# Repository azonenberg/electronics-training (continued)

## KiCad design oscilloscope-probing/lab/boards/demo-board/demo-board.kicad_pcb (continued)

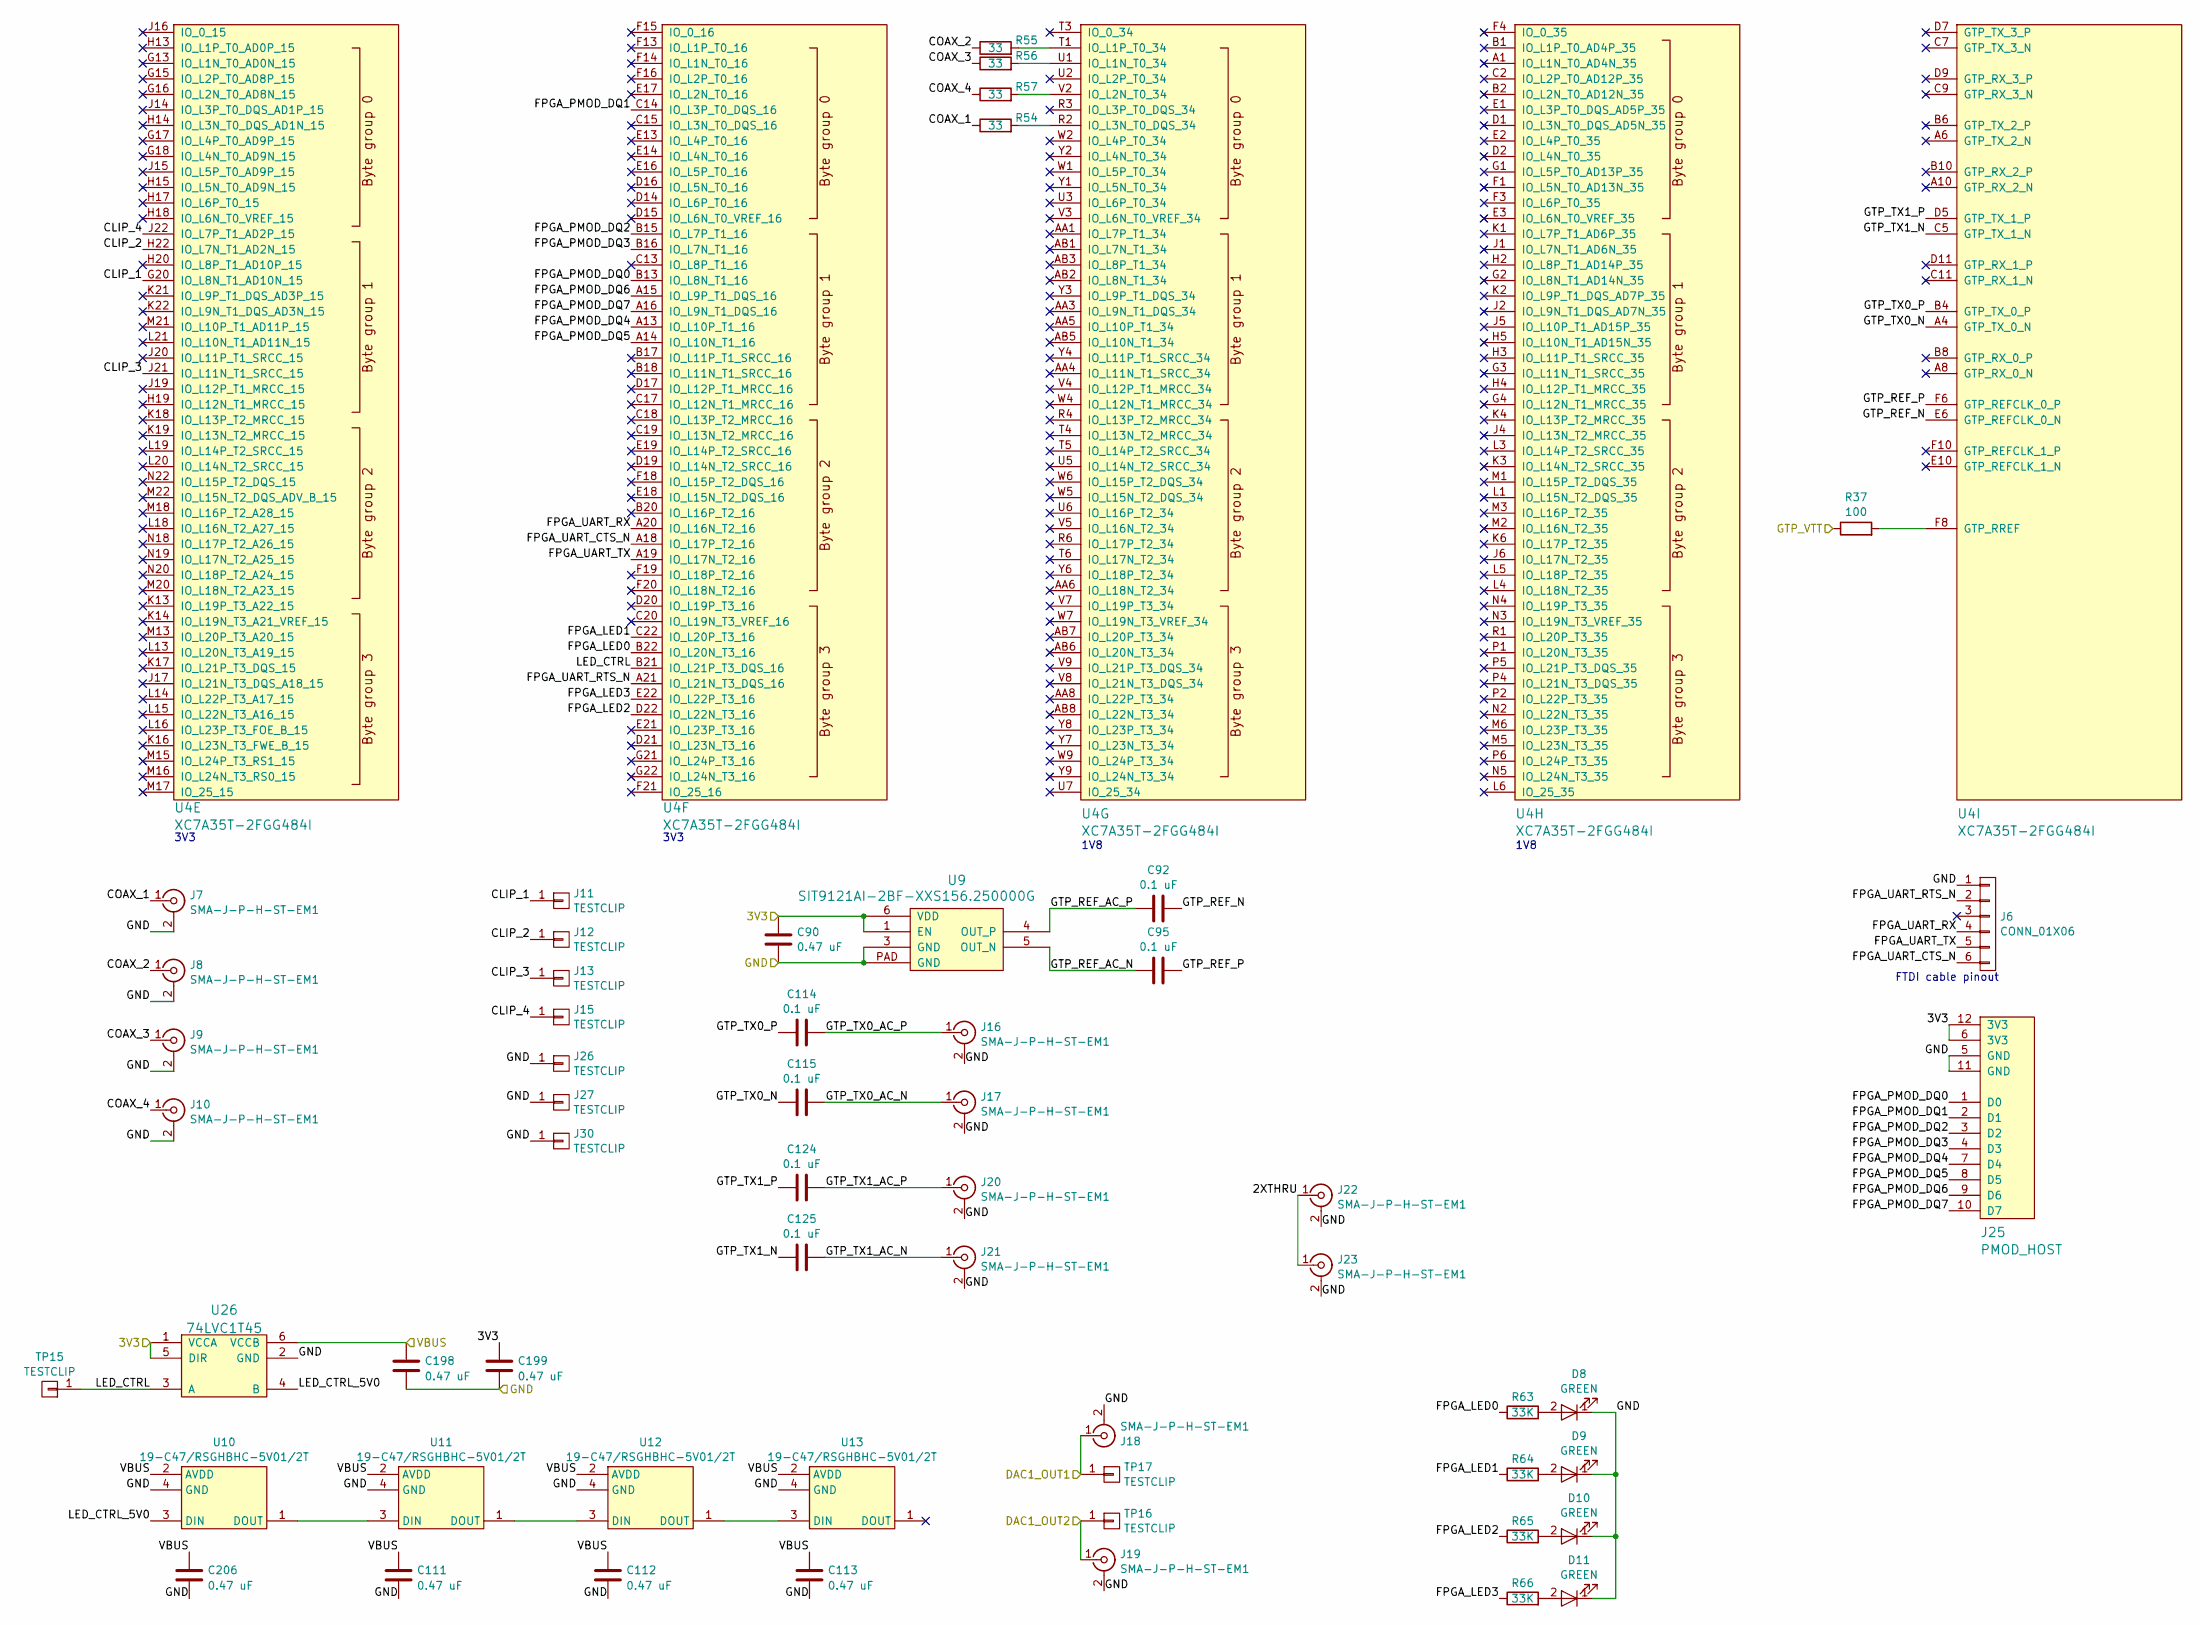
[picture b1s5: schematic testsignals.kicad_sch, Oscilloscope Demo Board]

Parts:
C90, C111, C112, C113, C198, C199, C206: 0.47 uF; EIA_0402_CAP_NOSILK
C92, C95, C114, C115, C124, C125: 0.1 uF; EIA_0402_CAP_NOSILK
D8, D9, D10, D11: GREEN; EIA_0402_LED
J6: CONN_01X06; CONN_HEADER_2.54MM_1x6_REFLOW
J7, J8, J9, J10, J16, J17, J20, J21: SMA-J-P-H-ST-EM1; CONN_SMA_EDGE_SAMTEC_SMA_J_P_H_ST_EM1
J11, J12, J13, J15, J26, J27, J30: TESTCLIP; TESTPOINT_SMT_KEYSTONE_5016
J18, J19, J22, J23: SMA-J-P-H-ST-EM1; CONN_SMA_EDGE_SAMTEC_SMA_J_P_H_ST_EM1_NOPASTE
J25: PMOD_HOST; CONN_HEADER_2.54MM_2x6_RA_PMOD_HOST
R37: 100; EIA_0402_RES_NOSILK
R54, R55, R56, R57: 33; EIA_0402_RES_NOSILK
R63, R64, R65, R66: 33K; EIA_0402_RES_NOSILK
TP15, TP16, TP17: TESTCLIP; TESTPOINT_SMT_KEYSTONE_5016
U4: XC7A35T-2FGG484I; BGA_484_22x22_FULLARRAY_1MM
U9: SIT9121AI-2BF-XXS156.250000G; OSCILLATOR_LVDS_3.2x2.5
U10, U11, U12, U13: 19-C47/RSGHBHC-5V01/2T; LED_EVERLIGHT_19-C47_RSGHBHC-5V01_2T
U26: 74LVC1T45; DFN_6_0.5MM_1.6x1.6MM_TI_DPK

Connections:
/1V2: R37.1; also elsewhere on the board
/3V3: C90.1, C199.1, J25.6 (3V3), J25.12 (3V3), U9.1 (EN), U9.6 (VDD), U26.1 (VCCA), U26.5 (DIR); also elsewhere on the board
/GND: C90.2, C111.2, C112.2, C113.2, C198.2, C199.2, C206.2, D8.1 (K), D9.1 (K), D10.1 (K), D11.1 (K), J6.1, J7.2 (Ext), J8.2 (Ext), J9.2 (Ext), J10.2 (Ext), J16.2 (Ext), J17.2 (Ext), J18.2 (Ext), J19.2 (Ext), J20.2 (Ext), J21.2 (Ext), J22.2 (Ext), J23.2 (Ext), J25.5 (GND), J25.11 (GND), J26.1, J27.1, J30.1, U9.3 (GND), U9.PAD (GND), U10.4 (GND), U11.4 (GND), U12.4 (GND), U13.4 (GND), U26.2 (GND); also elsewhere on the board
/MCU/DAC1_OUT1: J18.1 (In), TP17.1; also elsewhere on the board
/MCU/DAC1_OUT2: J19.1 (In), TP16.1; also elsewhere on the board
/Test signals/2XTHRU: J22.1 (In), J23.1 (In)
/Test signals/CLIP_1: J11.1, U4.G20 (IO_L8N_T1_AD10N_15)
/Test signals/CLIP_2: J12.1, U4.H22 (IO_L7N_T1_AD2N_15)
/Test signals/CLIP_3: J13.1, U4.J21 (IO_L11N_T1_SRCC_15)
/Test signals/CLIP_4: J15.1, U4.J22 (IO_L7P_T1_AD2P_15)
/Test signals/COAX_1: J7.1 (In), R54.1
/Test signals/COAX_2: J8.1 (In), R55.1
/Test signals/COAX_3: J9.1 (In), R56.1
/Test signals/COAX_4: J10.1 (In), R57.1
/Test signals/FPGA_LED0: R63.1, U4.B22 (IO_L20N_T3_16)
/Test signals/FPGA_LED1: R64.1, U4.C22 (IO_L20P_T3_16)
/Test signals/FPGA_LED2: R65.1, U4.D22 (IO_L22N_T3_16)
/Test signals/FPGA_LED3: R66.1, U4.E22 (IO_L22P_T3_16)
/Test signals/FPGA_PMOD_DQ0: J25.1 (D0), U4.B13 (IO_L8N_T1_16)
/Test signals/FPGA_PMOD_DQ1: J25.2 (D1), U4.C14 (IO_L3P_T0_DQS_16)
/Test signals/FPGA_PMOD_DQ2: J25.3 (D2), U4.B15 (IO_L7P_T1_16)
/Test signals/FPGA_PMOD_DQ3: J25.4 (D3), U4.B16 (IO_L7N_T1_16)
/Test signals/FPGA_PMOD_DQ4: J25.7 (D4), U4.A13 (IO_L10P_T1_16)
/Test signals/FPGA_PMOD_DQ5: J25.8 (D5), U4.A14 (IO_L10N_T1_16)
/Test signals/FPGA_PMOD_DQ6: J25.9 (D6), U4.A15 (IO_L9P_T1_DQS_16)
/Test signals/FPGA_PMOD_DQ7: J25.10 (D7), U4.A16 (IO_L9N_T1_DQS_16)
/Test signals/FPGA_UART_CTS_N: J6.6, U4.A18 (IO_L17P_T2_16)
/Test signals/FPGA_UART_RTS_N: J6.2, U4.A21 (IO_L21N_T3_DQS_16)
/Test signals/FPGA_UART_RX: J6.4, U4.A20 (IO_L16N_T2_16)
/Test signals/FPGA_UART_TX: J6.5, U4.A19 (IO_L17N_T2_16)
/Test signals/GTP_REF_AC_N: C95.1, U9.5 (OUT_N)
/Test signals/GTP_REF_AC_P: C92.1, U9.4 (OUT_P)
/Test signals/GTP_REF_N: C92.2, U4.E6 (GTP_REFCLK_0_N)
/Test signals/GTP_REF_P: C95.2, U4.F6 (GTP_REFCLK_0_P)
/Test signals/GTP_TX0_AC_N: C115.2, J17.1 (In)
/Test signals/GTP_TX0_AC_P: C114.2, J16.1 (In)
/Test signals/GTP_TX0_N: C115.1, U4.A4 (GTP_TX_0_N)
/Test signals/GTP_TX0_P: C114.1, U4.B4 (GTP_TX_0_P)
/Test signals/GTP_TX1_AC_N: C125.2, J21.1 (In)
/Test signals/GTP_TX1_AC_P: C124.2, J20.1 (In)
/Test signals/GTP_TX1_N: C125.1, U4.C5 (GTP_TX_1_N)
/Test signals/GTP_TX1_P: C124.1, U4.D5 (GTP_TX_1_P)
/Test signals/LED_CTRL: TP15.1, U4.B21 (IO_L21P_T3_DQS_16), U26.3 (A)
/Test signals/LED_CTRL_5V0: U10.3 (DIN), U26.4 (B)
/VBUS: C111.1, C112.1, C113.1, C198.1, C206.1, U10.2 (AVDD), U11.2 (AVDD), U12.2 (AVDD), U13.2 (AVDD), U26.6 (VCCB); also elsewhere on the board
unnamed: D8.2 (A), R63.2
unnamed: D9.2 (A), R64.2
unnamed: D10.2 (A), R65.2
unnamed: D11.2 (A), R66.2
unnamed: R56.2, U4.U1 (IO_L1N_T0_34)
unnamed: R55.2, U4.T1 (IO_L1P_T0_34)
unnamed: R57.2, U4.V2 (IO_L2N_T0_34)
unnamed: R54.2, U4.R2 (IO_L3N_T0_DQS_34)
unnamed: R37.2, U4.F8 (GTP_RREF)
unnamed: U10.1 (DOUT), U11.3 (DIN)
unnamed: U11.1 (DOUT), U12.3 (DIN)
unnamed: U12.1 (DOUT), U13.3 (DIN)

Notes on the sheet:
3V3
FTDI cable pinout
1V8

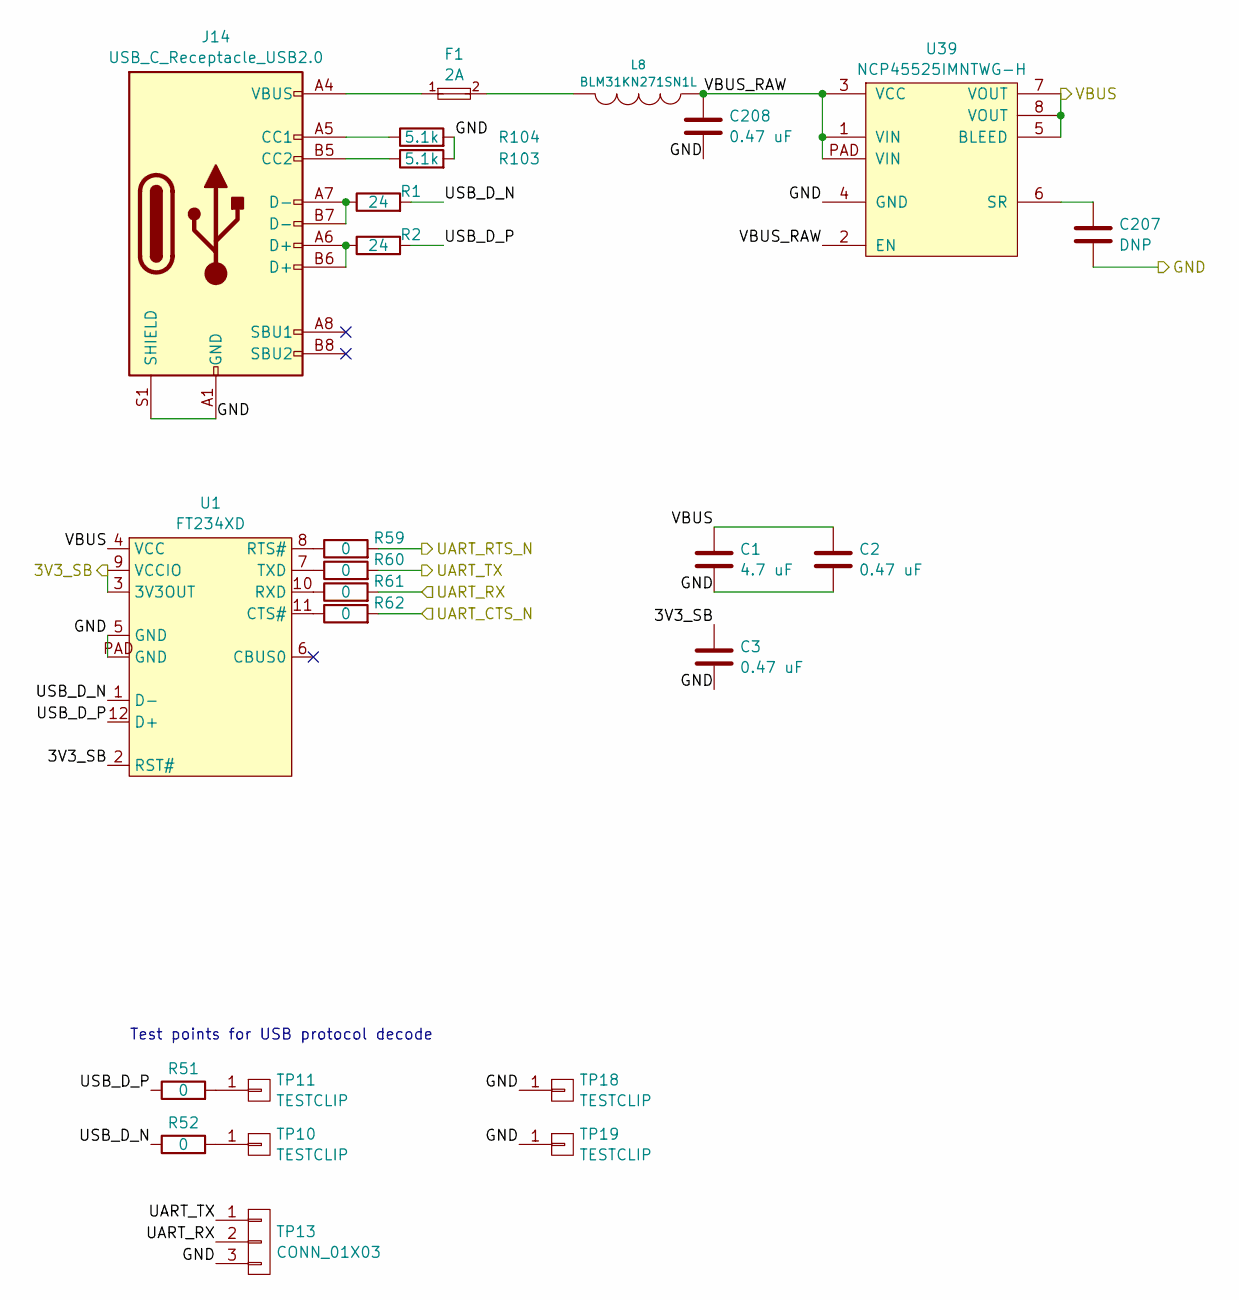
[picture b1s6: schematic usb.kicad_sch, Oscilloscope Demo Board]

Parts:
C1: 4.7 uF; EIA_0603_CAP_NOSILK
C2, C3, C208: 0.47 uF; EIA_0402_CAP_NOSILK
C207: DNP; EIA_0402_CAP_NOSILK
F1: 2A; EIA_0402_RES_NOSILK
J14: USB_C_Receptacle_USB2.0; GCT_USB4500-03-0-A
L8: BLM31KN271SN1L; EIA_1206_CAP_NOSILK
R1, R2: 24; EIA_0402_RES_NOSILK
R51, R52, R59, R60, R61, R62: 0; EIA_0402_RES_NOSILK
R103, R104: 5.1k; EIA_0402_RES_NOSILK
TP10, TP11, TP18, TP19: TESTCLIP; TESTPOINT_SMT_KEYSTONE_5016
TP13: CONN_01X03; CONN_HEADER_2.54MM_1x3_REFLOW
U1: FT234XD; DFN_12_0.5MM_3x3MM
U39: NCP45525IMNTWG-H; DFN_8_0.5MM_2x2MM

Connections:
/GND: C1.2, C2.2, C3.2, C207.2, C208.2, J14.A1 (GND), J14.A12 (GND), J14.B1 (GND), J14.B12 (GND), J14.S1 (SHIELD), R103.2, R104.2, TP13.3, TP18.1, TP19.1, U1.5 (GND), U1.PAD (GND), U39.4 (GND); also elsewhere on the board
/Power Supply/3V3_SB: C3.1, U1.2 (RST#), U1.3 (3V3OUT), U1.9 (VCCIO); also elsewhere on the board
/USB power inlet and UART/UART_CTS_N: R62.2; also elsewhere on the board
/USB power inlet and UART/UART_RTS_N: R59.2; also elsewhere on the board
/USB power inlet and UART/UART_RX: R61.2, TP13.2; also elsewhere on the board
/USB power inlet and UART/UART_TX: R60.2, TP13.1; also elsewhere on the board
/USB power inlet and UART/USB_D_N: R1.2, R52.1, U1.1 (D-)
/USB power inlet and UART/USB_D_P: R2.2, R51.1, U1.12 (D+)
/USB power inlet and UART/VBUS_RAW: C208.1, L8.1, U39.1 (VIN), U39.2 (EN), U39.3 (VCC), U39.PAD (VIN)
/VBUS: C1.1, C2.1, U1.4 (VCC), U39.5 (BLEED), U39.7 (VOUT), U39.8 (VOUT); also elsewhere on the board
unnamed: F1.1, J14.A4 (VBUS), J14.A9 (VBUS), J14.B4 (VBUS), J14.B9 (VBUS)
unnamed: F1.2, L8.2
unnamed: J14.A5 (CC1), R104.1
unnamed: J14.B5 (CC2), R103.1
unnamed: J14.A6 (D+), J14.B6 (D+), R2.1
unnamed: J14.A7 (D-), J14.B7 (D-), R1.1
unnamed: R52.2, TP10.1
unnamed: R51.2, TP11.1
unnamed: R62.1, U1.11 (CTS#)
unnamed: R59.1, U1.8 (RTS#)
unnamed: R61.1, U1.10 (RXD)
unnamed: R60.1, U1.7 (TXD)
unnamed: C207.1, U39.6 (SR)

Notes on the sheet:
Test points for USB protocol decode

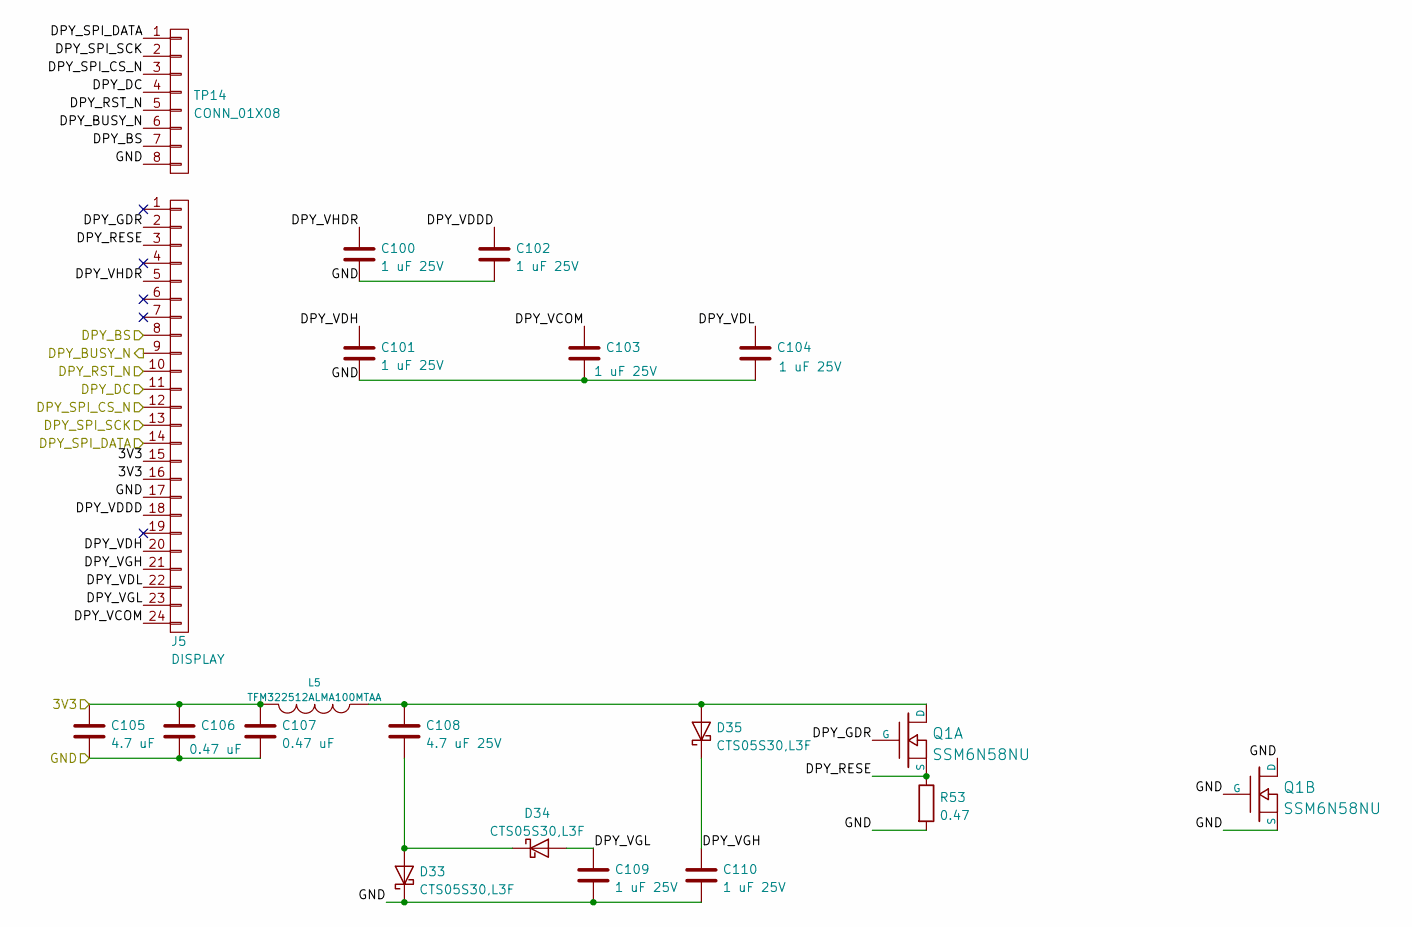
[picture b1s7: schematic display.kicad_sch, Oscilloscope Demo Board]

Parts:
C100, C101, C102, C103, C104, C109, C110: 1 uF 25V; EIA_0805_CAP_NOSILK
C105: 4.7 uF; EIA_0603_CAP_NOSILK
C106, C107: 0.47 uF; EIA_0402_CAP_NOSILK
C108: 4.7 uF 25V; EIA_0805_CAP_NOSILK
D33, D34, D35: CTS05S30,L3F; SOD882
J5: DISPLAY; CONN_FFC_0.5MM_1x24_HIROSE_FH34SRJ-24S-0.5SH(50)
L5: TFM322512ALMA100MTAA; EIA_1210_CAP_NOSILK
Q1: SSM6N58NU; DFN_6_0.65MM_2x2MM_GDS
R53: 0.47; EIA_0402_RES_NOSILK
TP14: CONN_01X08; CONN_HEADER_2.54MM_1x8

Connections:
/3V3: C105.1, C106.1, C107.1, J5.15, J5.16, L5.2; also elsewhere on the board
/GND: C100.2, C101.2, C102.2, C103.2, C104.2, C105.2, C106.2, C107.2, C109.2, C110.2, D33.1 (K), J5.17, Q1.D2 (D), Q1.G2 (G), Q1.S2 (S), R53.2, TP14.8; also elsewhere on the board
/MCU/DPY_BS: J5.8, TP14.7; also elsewhere on the board
/MCU/DPY_BUSY_N: J5.9, TP14.6; also elsewhere on the board
/MCU/DPY_DC: J5.11, TP14.4; also elsewhere on the board
/MCU/DPY_RST_N: J5.10, TP14.5; also elsewhere on the board
/MCU/DPY_SPI_CS_N: J5.12, TP14.3; also elsewhere on the board
/MCU/DPY_SPI_DATA: J5.14, TP14.1; also elsewhere on the board
/MCU/DPY_SPI_SCK: J5.13, TP14.2; also elsewhere on the board
/MCU/E-paper display/DPY_GDR: J5.2, Q1.G1 (G)
/MCU/E-paper display/DPY_RESE: J5.3, Q1.S1 (S), R53.1
/MCU/E-paper display/DPY_VCOM: C103.1, J5.24
/MCU/E-paper display/DPY_VDDD: C102.1, J5.18
/MCU/E-paper display/DPY_VDH: C101.1, J5.20
/MCU/E-paper display/DPY_VDL: C104.1, J5.22
/MCU/E-paper display/DPY_VGH: C110.1, D35.1 (K), J5.21
/MCU/E-paper display/DPY_VGL: C109.1, D34.2 (A), J5.23
/MCU/E-paper display/DPY_VHDR: C100.1, J5.5
unnamed: C108.2, D33.2 (A), D34.1 (K)
unnamed: C108.1, D35.2 (A), L5.1, Q1.D1 (D)

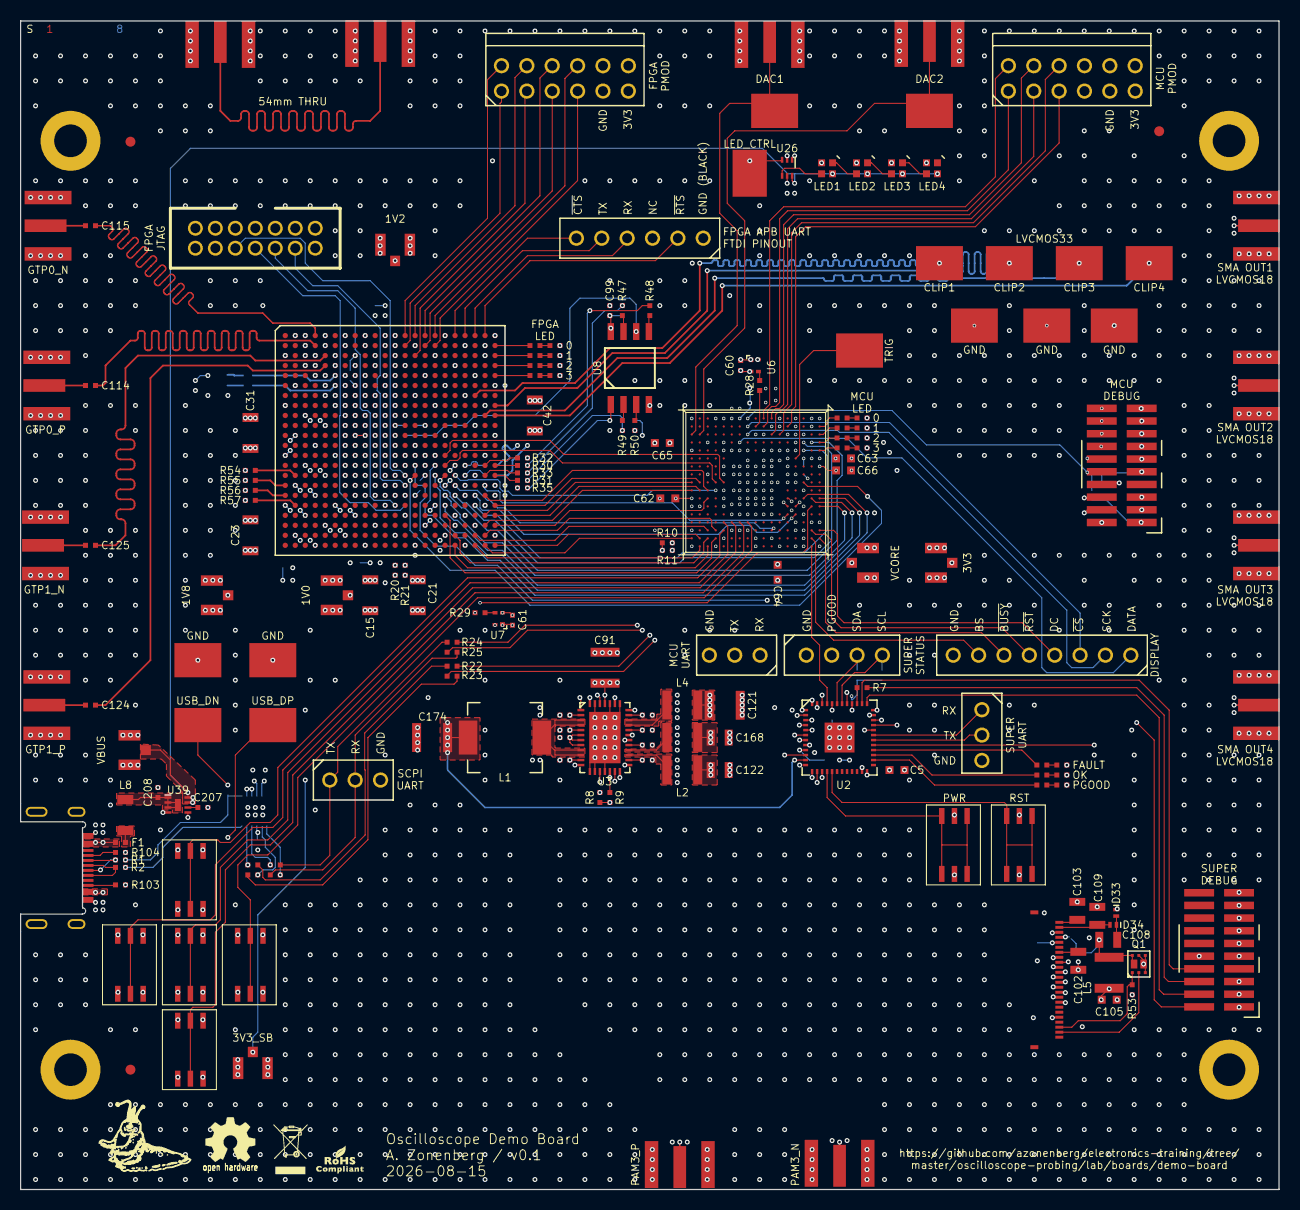
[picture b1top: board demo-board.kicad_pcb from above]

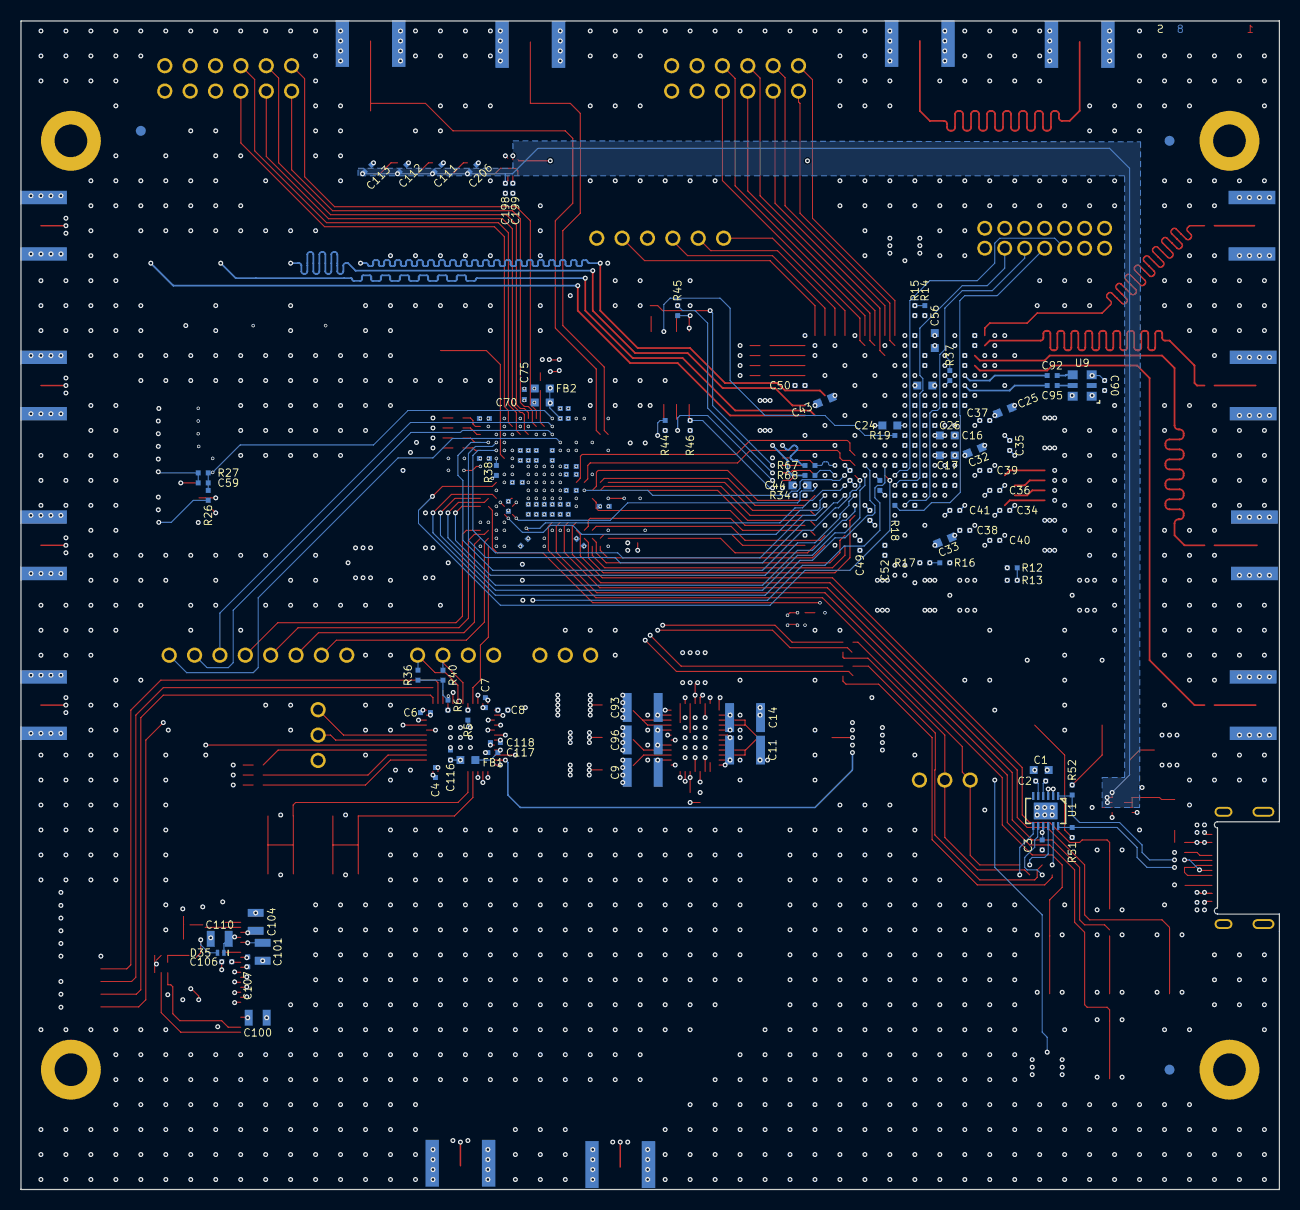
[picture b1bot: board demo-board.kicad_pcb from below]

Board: 8 copper layers, 126.0 x 117.0 mm, 311 parts (126 on the bottom side), 244 nets.

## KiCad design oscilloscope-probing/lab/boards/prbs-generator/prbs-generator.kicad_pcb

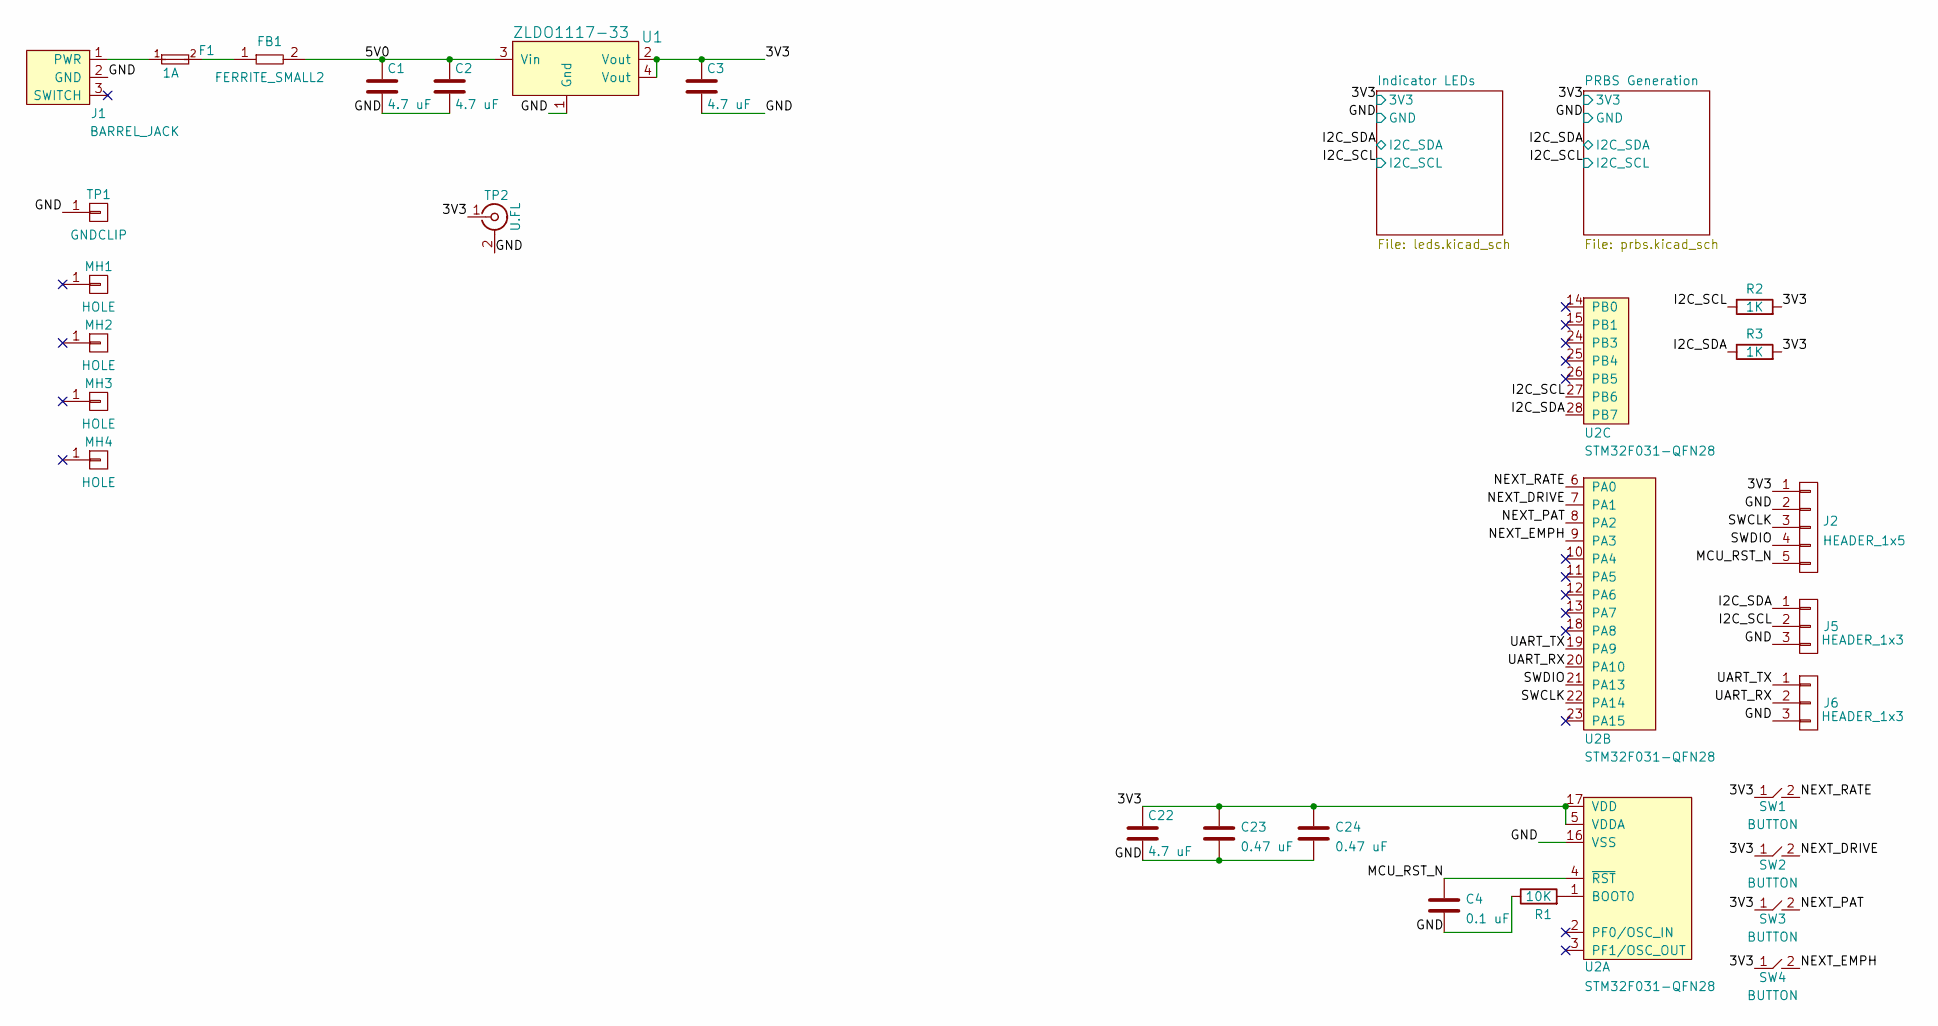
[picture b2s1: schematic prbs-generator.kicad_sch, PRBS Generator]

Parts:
C1, C2, C3, C22: 4.7 uF; EIA_0603_CAP_NOSILK
C4: 0.1 uF; EIA_0402_CAP_NOSILK
C23, C24: 0.47 uF; EIA_0402_CAP_NOSILK
F1: 1A; EIA_0402_CAP_NOSILK
FB1: FERRITE_SMALL2; EIA_0603_INDUCTOR_NOSILK
J1: BARREL_JACK; CONN_CUI_PJ-058BH_HIPWR_BARREL_NOSLOT
J2: HEADER_1x5; CONN_HEADER_2.54MM_1x5
J5, J6: HEADER_1x3; CONN_HEADER_2.54MM_1x3
MH1, MH2, MH3, MH4: HOLE; MECHANICAL_CLEARANCEHOLE_4_40
R1: 10K; EIA_0402_RES_NOSILK
R2, R3: 1K; EIA_0402_RES_NOSILK
SW1, SW2, SW3, SW4: BUTTON; SWITCH_RAFI_MICON_5
TP1: GNDCLIP; TESTPOINT_SMT_KEYSTONE_5016
TP2: U.FL; CONN_U.FL_TE_1909763-1
U1: ZLDO1117-33; SOT223-4
U2: STM32F031-QFN28; QFN_28_0.5MM_4x4MM_NOPAD

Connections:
/3V3: C3.1, C22.1, C23.1, C24.1, J2.1, R2.2, R3.2, SW1.1, SW2.1, SW3.1, SW4.1, TP2.1 (In), U1.2 (Vout), U1.4 (Vout), U2.5 (VDDA), U2.17 (VDD); also elsewhere on the board
/5V0: C1.1, C2.1, FB1.2, U1.3 (Vin)
/GND: C1.2, C2.2, C3.2, C4.2, C22.2, C23.2, C24.2, J1.2 (GND), J2.2, J5.3, J6.3, R1.1, TP1.1, TP2.2 (Ext), U1.1 (Gnd), U2.16 (VSS); also elsewhere on the board
/I2C_SCL: J5.2, R2.1, U2.27 (PB6); also elsewhere on the board
/I2C_SDA: J5.1, R3.1, U2.28 (PB7); also elsewhere on the board
/MCU_RST_N: C4.1, J2.5, U2.4 (~RST)
/NEXT_DRIVE: SW2.2, U2.7 (PA1)
/NEXT_EMPH: SW4.2, U2.9 (PA3)
/NEXT_PAT: SW3.2, U2.8 (PA2)
/NEXT_RATE: SW1.2, U2.6 (PA0)
/SWCLK: J2.3, U2.22 (PA14)
/SWDIO: J2.4, U2.21 (PA13)
/UART_RX: J6.2, U2.20 (PA10)
/UART_TX: J6.1, U2.19 (PA9)
unnamed: F1.1, J1.1 (PWR)
unnamed: F1.2, FB1.1
unnamed: R1.2, U2.1 (BOOT0)

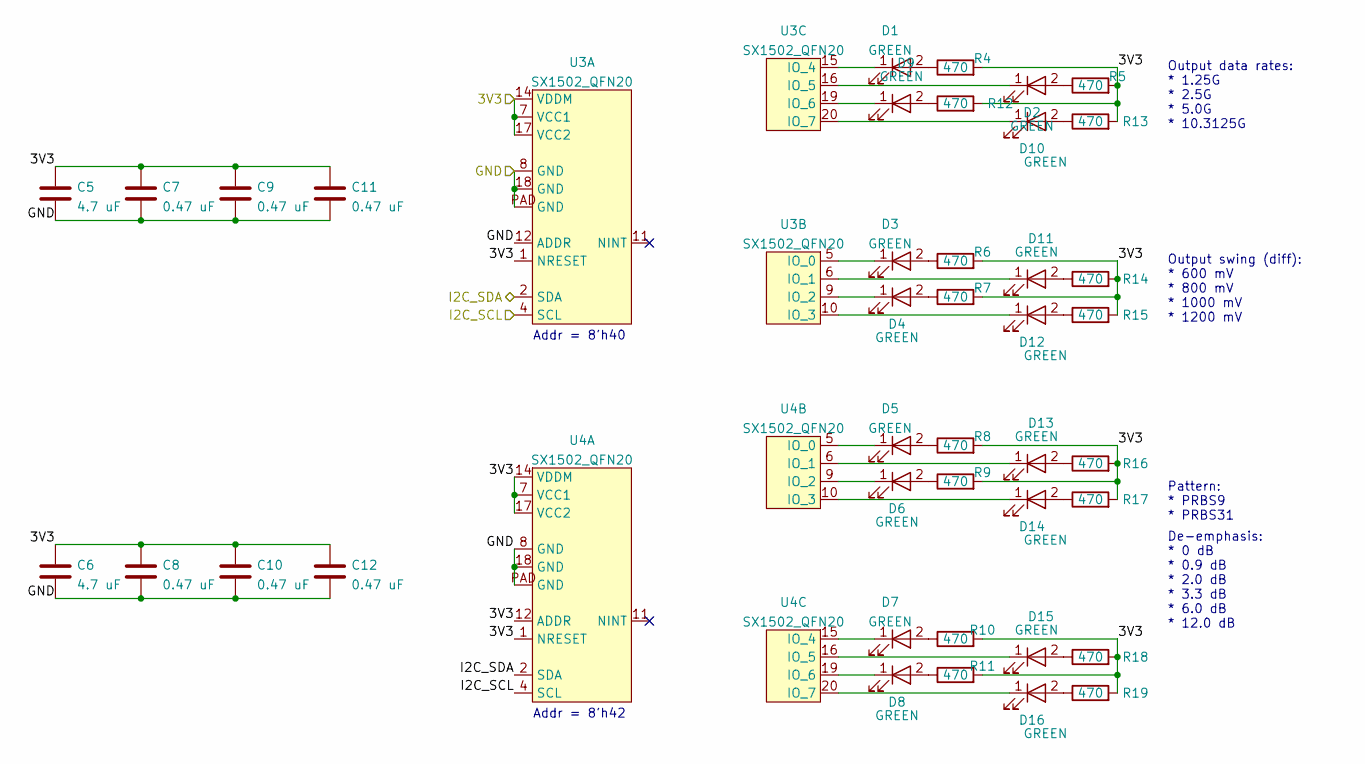
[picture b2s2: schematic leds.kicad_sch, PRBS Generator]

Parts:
C5, C6: 4.7 uF; EIA_0603_CAP_NOSILK
C7, C8, C9, C10, C11, C12: 0.47 uF; EIA_0402_CAP_NOSILK
D1, D2, D3, D4, D5, D6, D7, D8, D9, D10, D11, D12, D13, D14, D15, D16: GREEN; EIA_0805_LED
R4, R5, R6, R7, R8, R9, R10, R11, R12, R13, R14, R15, R16, R17, R18, R19: 470; EIA_0402_RES_NOSILK
U3, U4: SX1502_QFN20; QFN_20_0.4MM_3x3MM

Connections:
/3V3: C5.1, C6.1, C7.1, C8.1, C9.1, C10.1, C11.1, C12.1, R4.2, R5.2, R6.2, R7.2, R8.2, R9.2, R10.2, R11.2, R12.2, R13.2, R14.2, R15.2, R16.2, R17.2, R18.2, R19.2, U3.1 (NRESET), U3.7 (VCC1), U3.14 (VDDM), U3.17 (VCC2), U4.1 (NRESET), U4.7 (VCC1), U4.12 (ADDR), U4.14 (VDDM), U4.17 (VCC2); also elsewhere on the board
/GND: C5.2, C6.2, C7.2, C8.2, C9.2, C10.2, C11.2, C12.2, U3.8 (GND), U3.12 (ADDR), U3.18 (GND), U3.PAD (GND), U4.8 (GND), U4.18 (GND), U4.PAD (GND); also elsewhere on the board
/I2C_SCL: U3.4 (SCL), U4.4 (SCL); also elsewhere on the board
/I2C_SDA: U3.2 (SDA), U4.2 (SDA); also elsewhere on the board
unnamed: D1.1 (K), U3.15 (IO_4)
unnamed: D1.2 (A), R4.1
unnamed: D2.1 (K), U3.16 (IO_5)
unnamed: D2.2 (A), R5.1
unnamed: D3.1 (K), U3.5 (IO_0)
unnamed: D3.2 (A), R6.1
unnamed: D4.1 (K), U3.9 (IO_2)
unnamed: D4.2 (A), R7.1
unnamed: D5.1 (K), U4.5 (IO_0)
unnamed: D5.2 (A), R8.1
unnamed: D6.1 (K), U4.9 (IO_2)
unnamed: D6.2 (A), R9.1
unnamed: D7.1 (K), U4.15 (IO_4)
unnamed: D7.2 (A), R10.1
unnamed: D8.1 (K), U4.19 (IO_6)
unnamed: D8.2 (A), R11.1
unnamed: D9.1 (K), U3.19 (IO_6)
unnamed: D9.2 (A), R12.1
unnamed: D10.1 (K), U3.20 (IO_7)
unnamed: D10.2 (A), R13.1
unnamed: D11.1 (K), U3.6 (IO_1)
unnamed: D11.2 (A), R14.1
unnamed: D12.1 (K), U3.10 (IO_3)
unnamed: D12.2 (A), R15.1
unnamed: D13.1 (K), U4.6 (IO_1)
unnamed: D13.2 (A), R16.1
unnamed: D14.1 (K), U4.10 (IO_3)
unnamed: D14.2 (A), R17.1
unnamed: D15.1 (K), U4.16 (IO_5)
unnamed: D15.2 (A), R18.1
unnamed: D16.1 (K), U4.20 (IO_7)
unnamed: D16.2 (A), R19.1

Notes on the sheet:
Pattern: * PRBS9 * PRBS31
Addr = 8'h42
Addr = 8'h40
Output data rates: * 1.25G * 2.5G * 5.0G * 10.3125G
Output swing (diff): * 600 mV * 800 mV * 1000 mV * 1200 mV
De-emphasis: * 0 dB * 0.9 dB * 2.0 dB * 3.3 dB * 6.0 dB * 12.0 dB

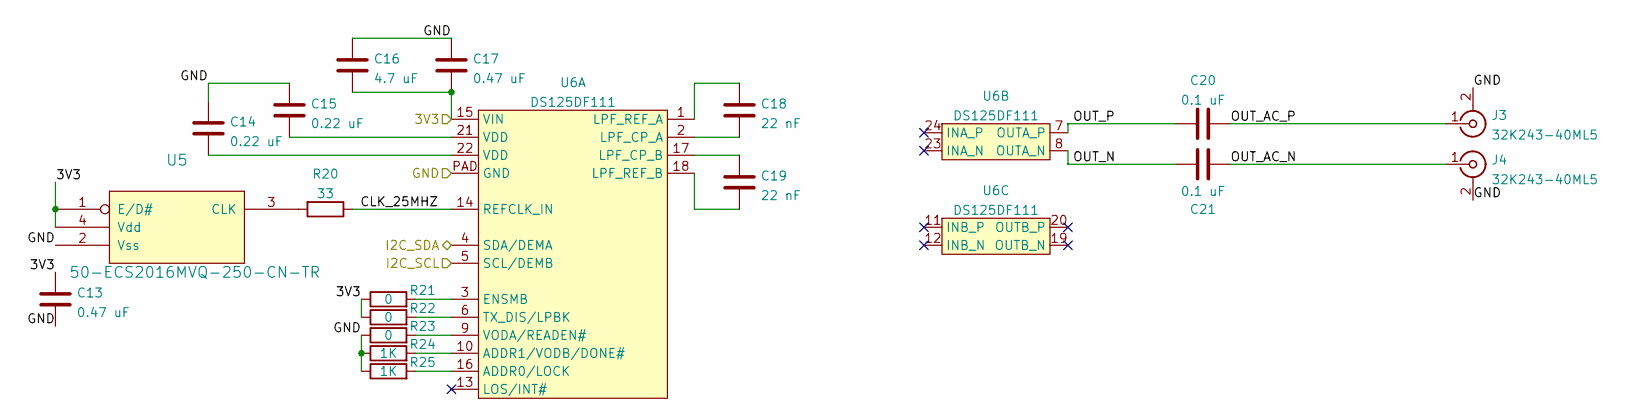
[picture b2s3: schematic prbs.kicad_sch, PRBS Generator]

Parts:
C13, C17: 0.47 uF; EIA_0402_CAP_NOSILK
C14, C15: 0.22 uF; EIA_0402_CAP_NOSILK
C16: 4.7 uF; EIA_0603_CAP_NOSILK
C18, C19: 22 nF; EIA_0805_CAP_NOSILK
C20, C21: 0.1 uF; EIA_0402_CAP_NOSILK
J3, J4: 32K243-40ML5; CONN_SMA_EDGE_ROSENBERGER_32K243_40ML5
R20: 33; EIA_0402_RES_NOSILK
R21, R22, R23: 0; EIA_0402_RES_NOSILK
R24, R25: 1K; EIA_0402_RES_NOSILK
U5: 50-ECS2016MVQ-250-CN-TR; OSCILLATOR_1.6x1.2
U6: DS125DF111; QFN_24_0.5MM_4x4MM

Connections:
/3V3: C13.1, C16.2, C17.2, R21.1, R22.1, U5.1 (E/D#), U5.4 (Vdd), U6.15 (VIN); also elsewhere on the board
/GND: C13.2, C14.1, C15.1, C16.1, C17.1, J3.2 (Ext), J4.2 (Ext), R23.1, R24.1, R25.1, U5.2 (Vss), U6.PAD (GND); also elsewhere on the board
/I2C_SCL: U6.5 (SCL/DEMB); also elsewhere on the board
/I2C_SDA: U6.4 (SDA/DEMA); also elsewhere on the board
/PRBS Generation/CLK_25MHZ: R20.1, U6.14 (REFCLK_IN)
/PRBS Generation/OUT_AC_N: C21.1, J4.1 (In)
/PRBS Generation/OUT_AC_P: C20.1, J3.1 (In)
/PRBS Generation/OUT_N: C21.2, U6.8 (OUTA_N)
/PRBS Generation/OUT_P: C20.2, U6.7 (OUTA_P)
unnamed: C14.2, U6.22 (VDD)
unnamed: C15.2, U6.21 (VDD)
unnamed: C18.1, U6.1 (LPF_REF_A)
unnamed: C18.2, U6.2 (LPF_CP_A)
unnamed: C19.1, U6.17 (LPF_CP_B)
unnamed: C19.2, U6.18 (LPF_REF_B)
unnamed: R20.2, U5.3 (CLK)
unnamed: R21.2, U6.3 (ENSMB)
unnamed: R22.2, U6.6 (TX_DIS/LPBK)
unnamed: R23.2, U6.9 (VODA/READEN#)
unnamed: R24.2, U6.10 (ADDR1/VODB/DONE#)
unnamed: R25.2, U6.16 (ADDR0/LOCK)
